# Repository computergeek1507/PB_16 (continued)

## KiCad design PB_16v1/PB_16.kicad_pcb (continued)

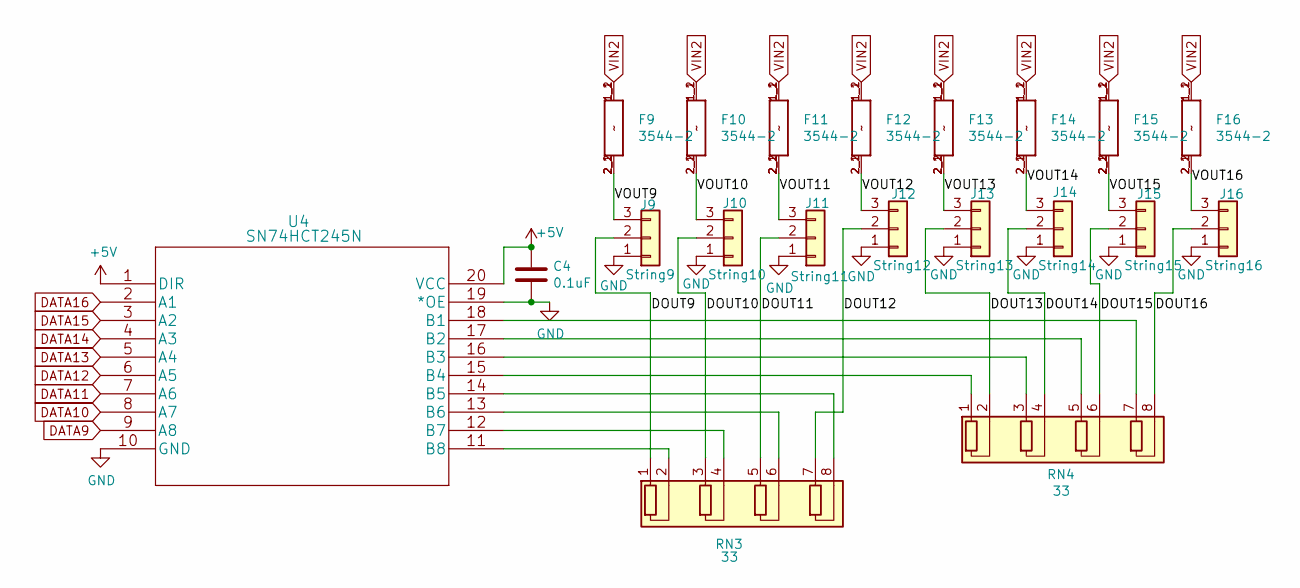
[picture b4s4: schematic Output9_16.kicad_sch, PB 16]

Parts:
C4: 0.1uF; C_Rect_L7.0mm_W2.0mm_P5.00mm; MPN SR215C104KARTR1; Digi-Key_PN 478-7336-1-ND
F9, F10, F11, F12, F13, F14, F15, F16: 3544-2; FUSE_3544-2; MPN 3544-2; Digi-Key_PN 36-3544-2-ND
J9: String9; PhoenixContact_MCV_1,5_3-G-3.5_1x03_P3.50mm_Vertical; MPN 1843619/OSTTJ0311530; Digi-Key_PN 277-5737-ND/ED10555-ND
J10: String10; PhoenixContact_MCV_1,5_3-G-3.5_1x03_P3.50mm_Vertical; MPN 1843619/OSTTJ0311530; Digi-Key_PN 277-5737-ND/ED10555-ND
J11: String11; PhoenixContact_MCV_1,5_3-G-3.5_1x03_P3.50mm_Vertical; MPN 1843619/OSTTJ0311530; Digi-Key_PN 277-5737-ND/ED10555-ND
J12: String12; PhoenixContact_MCV_1,5_3-G-3.5_1x03_P3.50mm_Vertical; MPN 1843619/OSTTJ0311530; Digi-Key_PN 277-5737-ND/ED10555-ND
J13: String13; PhoenixContact_MCV_1,5_3-G-3.5_1x03_P3.50mm_Vertical; MPN 1843619/OSTTJ0311530; Digi-Key_PN 277-5737-ND/ED10555-ND
J14: String14; PhoenixContact_MCV_1,5_3-G-3.5_1x03_P3.50mm_Vertical; MPN 1843619/OSTTJ0311530; Digi-Key_PN 277-5737-ND/ED10555-ND
J15: String15; PhoenixContact_MCV_1,5_3-G-3.5_1x03_P3.50mm_Vertical; MPN 1843619/OSTTJ0311530; Digi-Key_PN 277-5737-ND/ED10555-ND
J16: String16; PhoenixContact_MCV_1,5_3-G-3.5_1x03_P3.50mm_Vertical; MPN 1843619/OSTTJ0311530; Digi-Key_PN 277-5737-ND/ED10555-ND
RN3, RN4: 33; R_Array_SIP8; MPN 4608X-102-330LF; Digi-Key_PN 4608X-2-330LF-ND
U4: SN74HCT245N; MPN SN74HCT245N; Digi-Key_PN 296-1612-5-ND

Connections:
+5V: C4.1, U4.1 (DIR), U4.20 (VCC); also elsewhere on the board
/Output 9-16/DOUT9: J9.2, RN3.1 (R1.1)
/Output 9-16/DOUT10: J10.2, RN3.3 (R2.1)
/Output 9-16/DOUT11: J11.2, RN3.5 (R3.1)
/Output 9-16/DOUT12: J12.2, RN3.7 (R4.1)
/Output 9-16/DOUT13: J13.2, RN4.2 (R1.2)
/Output 9-16/DOUT14: J14.2, RN4.4 (R2.2)
/Output 9-16/DOUT15: J15.2, RN4.6 (R3.2)
/Output 9-16/DOUT16: J16.2, RN4.8 (R4.2)
/Output 9-16/VOUT9: F9.2_1 (2), F9.2_2 (2), J9.3
/Output 9-16/VOUT10: F10.2_1 (2), F10.2_2 (2), J10.3
/Output 9-16/VOUT11: F11.2_1 (2), F11.2_2 (2), J11.3
/Output 9-16/VOUT12: F12.2_1 (2), F12.2_2 (2), J12.3
/Output 9-16/VOUT13: F13.2_1 (2), F13.2_2 (2), J13.3
/Output 9-16/VOUT14: F14.2_1 (2), F14.2_2 (2), J14.3
/Output 9-16/VOUT15: F15.2_1 (2), F15.2_2 (2), J15.3
/Output 9-16/VOUT16: F16.2_1 (2), F16.2_2 (2), J16.3
DATA9: U4.9 (A8); also elsewhere on the board
DATA10: U4.8 (A7); also elsewhere on the board
DATA11: U4.7 (A6); also elsewhere on the board
DATA12: U4.6 (A5); also elsewhere on the board
DATA13: U4.5 (A4); also elsewhere on the board
DATA14: U4.4 (A3); also elsewhere on the board
DATA15: U4.3 (A2); also elsewhere on the board
DATA16: U4.2 (A1); also elsewhere on the board
GND: C4.2, J9.1, J10.1, J11.1, J12.1, J13.1, J14.1, J15.1, J16.1, U4.10 (GND), U4.19 (*OE); also elsewhere on the board
unnamed: RN3.2 (R1.2), U4.11 (B8)
unnamed: RN3.4 (R2.2), U4.12 (B7)
unnamed: RN3.6 (R3.2), U4.13 (B6)
unnamed: RN3.8 (R4.2), U4.14 (B5)
unnamed: RN4.1 (R1.1), U4.15 (B4)
unnamed: RN4.3 (R2.1), U4.16 (B3)
unnamed: RN4.5 (R3.1), U4.17 (B2)
unnamed: RN4.7 (R4.1), U4.18 (B1)
VIN2: F9.1_1 (1), F9.1_2 (1), F10.1_1 (1), F10.1_2 (1), F11.1_1 (1), F11.1_2 (1), F12.1_1 (1), F12.1_2 (1), F13.1_1 (1), F13.1_2 (1), F14.1_1 (1), F14.1_2 (1), F15.1_1 (1), F15.1_2 (1), F16.1_1 (1), F16.1_2 (1); also elsewhere on the board

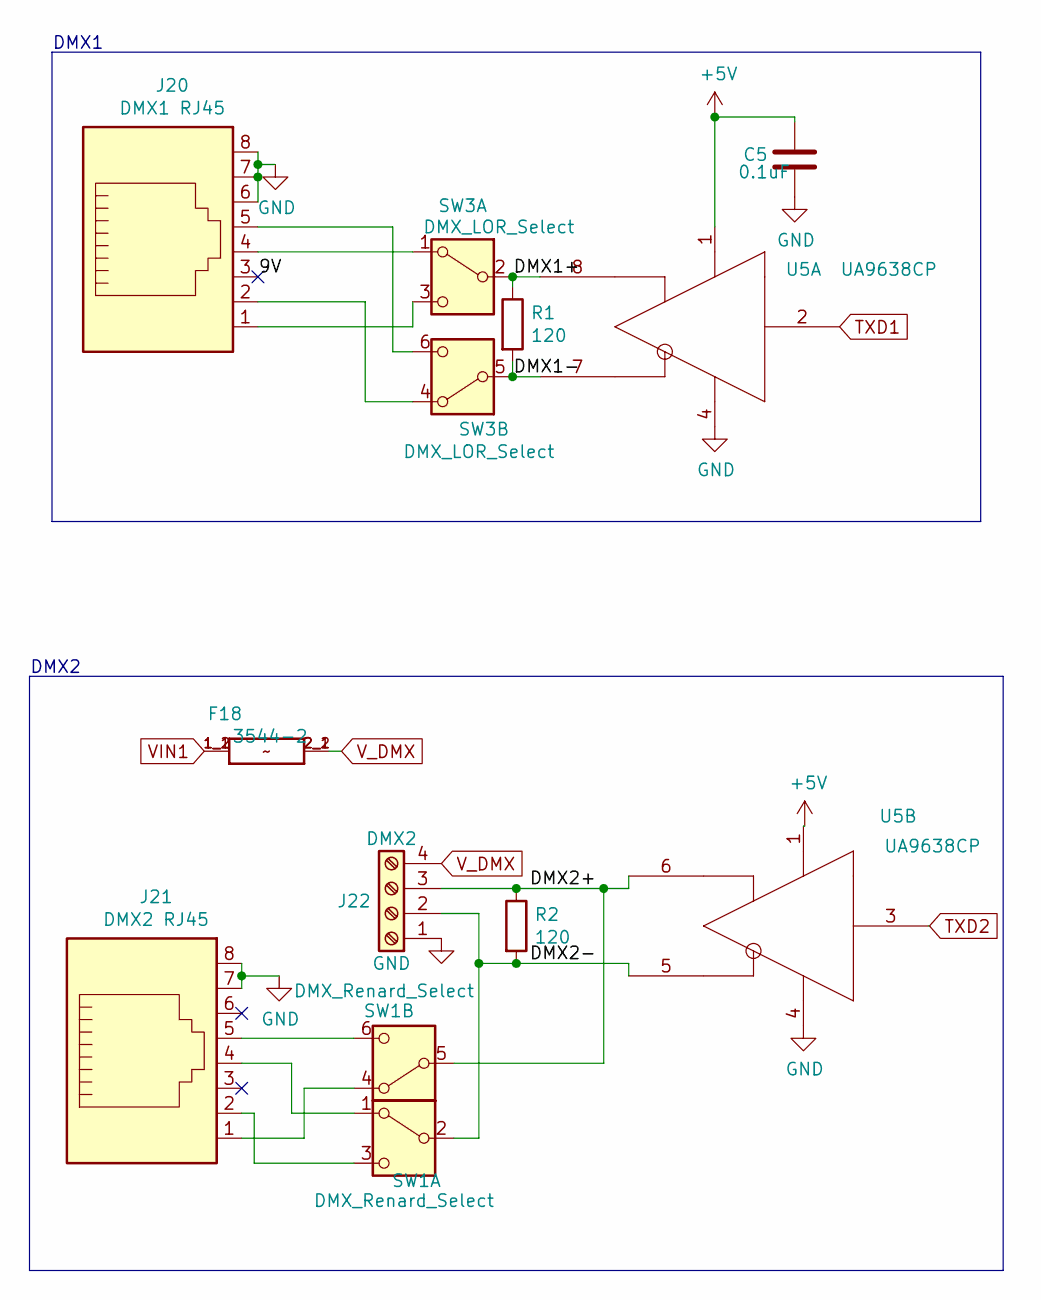
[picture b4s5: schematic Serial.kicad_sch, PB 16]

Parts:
C5: 0.1uF; C_Rect_L7.0mm_W2.0mm_P5.00mm; MPN SR215C104KARTR1; Digi-Key_PN 478-7336-1-ND
F18: 3544-2; FUSE_3544-2; MPN 3544-2; Digi-Key_PN 36-3544-2-ND
J20: DMX1 RJ45; RJ45_Amphenol_54602-x08_Horizontal; MPN A-2014-2-4-R; Digi-Key_PN AE10392-ND
J21: DMX2 RJ45; RJ45_Amphenol_54602-x08_Horizontal; MPN A-2014-2-4-R; Digi-Key_PN AE10392-ND
J22: DMX2; TerminalBlock_Phoenix_MKDS-1,5-4_1x04_P5.00mm_Horizontal; MPN 1729034; Digi-Key_PN 277-1238-ND
R1, R2: 120; R_Axial_DIN0207_L6.3mm_D2.5mm_P7.62mm_Horizontal; MPN CF14JT120R; Digi-Key_PN CF14JT120RCT-ND
SW1: DMX_Renard_Select; SW_CK_JS202011CQN_DPDT_Straight; MPN JS202011CQN; Digi-Key_PN 401-2001-ND
SW3: DMX_LOR_Select; SW_CK_JS202011CQN_DPDT_Straight; MPN JS202011CQN; Digi-Key_PN 401-2001-ND
U5: UA9638CP; DIP-8_W7.62mm; MPN UA9638CP; Digi-Key_PN 296-15059-5-ND

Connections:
+5V: C5.1, U5.1 (VCC); also elsewhere on the board
/Serial/9V: J20.3
/Serial/DMX1+: R1.1, SW3.2 (B), U5.8 (OUTB)
/Serial/DMX1-: R1.2, SW3.5 (B), U5.7 (OUTA)
/Serial/DMX2+: J22.3, R2.1, SW1.5 (B), U5.6 (OUTB)
/Serial/DMX2-: J22.2, R2.2, SW1.2 (B), U5.5 (OUTA)
GND: C5.2, J20.6, J20.7, J20.8, J21.7, J21.8, J22.1, U5.4 (GND); also elsewhere on the board
unnamed: J21.4, SW1.1 (A)
unnamed: J21.2, SW1.3 (C)
unnamed: J21.1, SW1.4 (A)
unnamed: J21.5, SW1.6 (C)
unnamed: J20.4, SW3.1 (A)
unnamed: J20.1, SW3.3 (C)
unnamed: J20.2, SW3.4 (A)
unnamed: J20.5, SW3.6 (C)
TXD1: U5.2 (IN); also elsewhere on the board
TXD2: U5.3 (IN); also elsewhere on the board
VIN1: F18.1_1 (1), F18.1_2 (1); also elsewhere on the board
V_DMX: F18.2_1 (2), F18.2_2 (2), J22.4

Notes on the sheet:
DMX2
DMX1

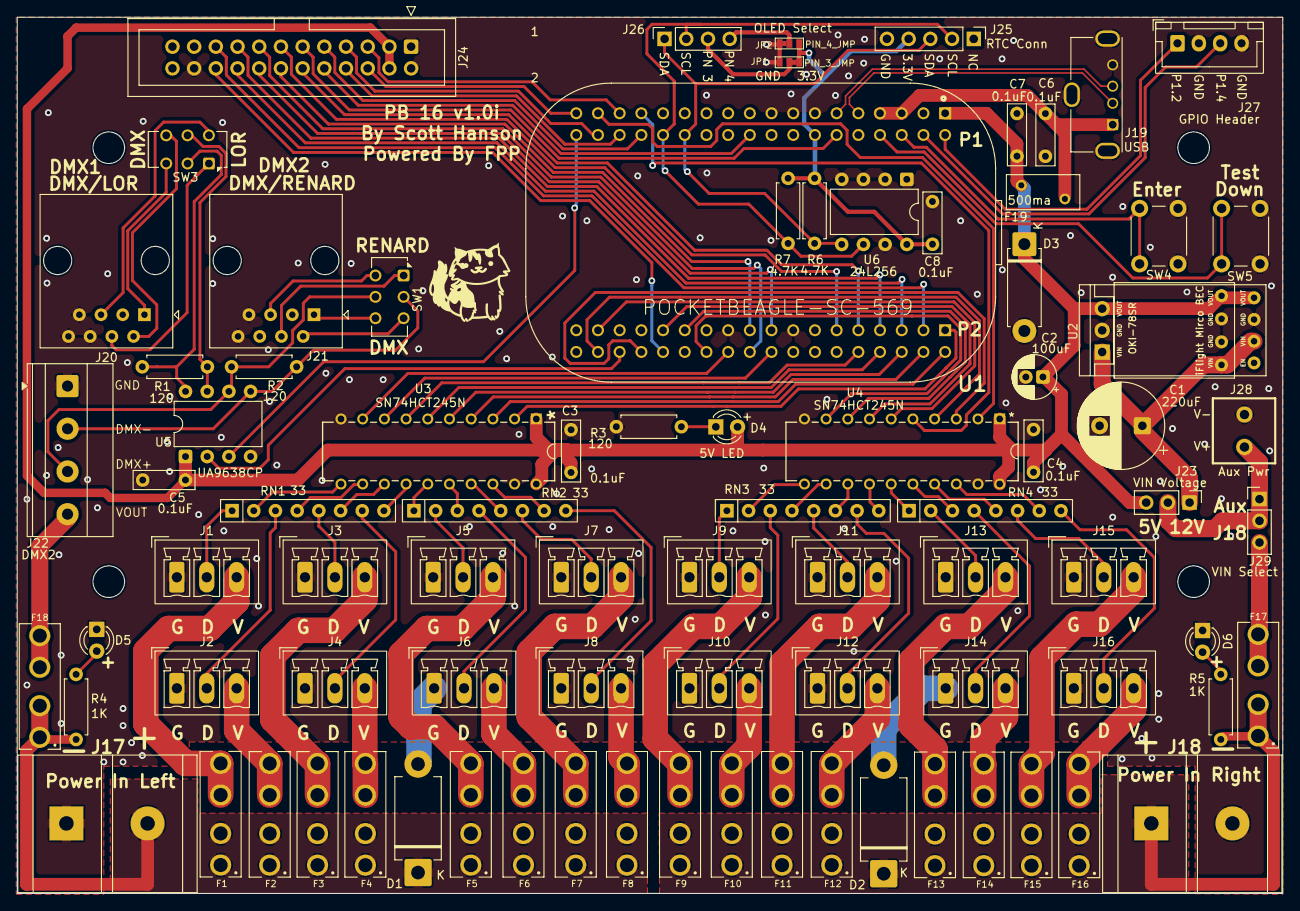
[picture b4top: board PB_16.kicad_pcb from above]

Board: 2 copper layers, 148.1 x 102.6 mm, 89 parts (0 on the bottom side), 117 nets.

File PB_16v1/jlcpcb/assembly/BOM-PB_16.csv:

Comment,Designator,Footprint,LCSC
100uF,C2,CP_Radial_D5.0mm_P2.00mm,
0.1uF,C4,C_Rect_L7.0mm_W2.0mm_P5.00mm,
String2,J2,"PhoenixContact_MCV_1,5_3-G-3.5_1x03_P3.50mm_Vertical",
String5,J5,"PhoenixContact_MCV_1,5_3-G-3.5_1x03_P3.50mm_Vertical",
String6,J6,"PhoenixContact_MCV_1,5_3-G-3.5_1x03_P3.50mm_Vertical",
String7,J7,"PhoenixContact_MCV_1,5_3-G-3.5_1x03_P3.50mm_Vertical",
String8,J8,"PhoenixContact_MCV_1,5_3-G-3.5_1x03_P3.50mm_Vertical",
String9,J9,"PhoenixContact_MCV_1,5_3-G-3.5_1x03_P3.50mm_Vertical",
String10,J10,"PhoenixContact_MCV_1,5_3-G-3.5_1x03_P3.50mm_Vertical",
String11,J11,"PhoenixContact_MCV_1,5_3-G-3.5_1x03_P3.50mm_Vertical",
String12,J12,"PhoenixContact_MCV_1,5_3-G-3.5_1x03_P3.50mm_Vertical",
String13,J13,"PhoenixContact_MCV_1,5_3-G-3.5_1x03_P3.50mm_Vertical",
String14,J14,"PhoenixContact_MCV_1,5_3-G-3.5_1x03_P3.50mm_Vertical",
String15,J15,"PhoenixContact_MCV_1,5_3-G-3.5_1x03_P3.50mm_Vertical",
String16,J16,"PhoenixContact_MCV_1,5_3-G-3.5_1x03_P3.50mm_Vertical",
SN74HCT245N,U4,SN74HCT245N,
3544-2,F1,FUSE_3544-2,
3544-2,F7,FUSE_3544-2,
3544-2,F14,FUSE_3544-2,
SB5100-T,D2,D_DO-201AD_P12.70mm_Horizontal,
0.1uF,C3,C_Rect_L7.0mm_W2.0mm_P5.00mm,
3544-2,F2,FUSE_3544-2,
3544-2,F6,FUSE_3544-2,
3544-2,F8,FUSE_3544-2,
3544-2,F9,FUSE_3544-2,
3544-2,F10,FUSE_3544-2,
3544-2,F16,FUSE_3544-2,
3544-2,F5,FUSE_3544-2,
3544-2,F3,FUSE_3544-2,
3544-2,F13,FUSE_3544-2,
33,RN1,R_Array_SIP8,
3544-2,F11,FUSE_3544-2,
33,RN3,R_Array_SIP8,
33,RN4,R_Array_SIP8,
33,RN2,R_Array_SIP8,
3544-2,F4,FUSE_3544-2,
String1,J1,"PhoenixContact_MCV_1,5_3-G-3.5_1x03_P3.50mm_Vertical",
String3,J3,"PhoenixContact_MCV_1,5_3-G-3.5_1x03_P3.50mm_Vertical",
String4,J4,"PhoenixContact_MCV_1,5_3-G-3.5_1x03_P3.50mm_Vertical",
SB5100-T,D1,D_DO-201AD_P12.70mm_Horizontal,
USB,J19,USB_A_Molex_105057_Vertical,
120,R1,R_Axial_DIN0207_L6.3mm_D2.5mm_P7.62mm_Horizontal,
120,R2,R_Axial_DIN0207_L6.3mm_D2.5mm_P7.62mm_Horizontal,
RTC Conn,J25,PinHeader_1x05_P2.54mm_Vertical,
3544-2,F15,FUSE_3544-2,
3544-2,F12,FUSE_3544-2,
Expansion Header,J24,IDC-Header_2x20_P2.54mm_Vertical,
Universe5V,U2,Universal_5V_Horizontal,
SN74HCT245N,U3,SN74HCT245N,
500ma,F19,Fuse_BelFuse_0ZRE0005FF_L8.3mm_W3.8mm,
DMX_Renard_Select,SW1,SW_CuK_JS202011CQN_DPDT_Straight,
0.1uF,C6,C_Rect_L7.0mm_W2.0mm_P5.00mm,
0.1uF,C7,C_Rect_L7.0mm_W2.0mm_P5.00mm,
POCKETBEAGLE-SC-569,U1,BEAGLE_POCKETBEAGLE-SC-569,
OLED Select,J26,PinSocket_1x04_P2.54mm_Vertical,
DMX2 RJ45,J21,RJ45_Amphenol_54602-x08_Horizontal,
VIN1 LED,D5,LED_D3.0mm_Clear,
VIN2 LED,D6,LED_D3.0mm_Clear,
1K,R4,R_Axial_DIN0207_L6.3mm_D2.5mm_P7.62mm_Horizontal,
1K,R5,R_Axial_DIN0207_L6.3mm_D2.5mm_P7.62mm_Horizontal,
VIN Voltage,J23,PinHeader_1x03_P2.54mm_Vertical,
5V LED,D4,LED_D3.0mm_Clear,
120,R3,R_Axial_DIN0207_L6.3mm_D2.5mm_P7.62mm_Horizontal,
GPIO Header,J27,JST_XH_B4B-XH-A_1x04_P2.50mm_Vertical,
OLED Select,SW2,SW_CuK_JS202011CQN_DPDT_Straight,
3544-2,F17,FUSE_3544-2,
VIN Select,J29,PinHeader_1x03_P2.54mm_Vertical,
Aux Pwr,J28,PHOENIX_MKDS1%2f2-3.81,
220uF,C1,CP_Radial_D10.0mm_P5.00mm,
4.7K,R6,R_Axial_DIN0207_L6.3mm_D2.5mm_P7.62mm_Horizontal,
4.7K,R7,R_Axial_DIN0207_L6.3mm_D2.5mm_P7.62mm_Horizontal,
24L256,U6,DIP-8_W7.62mm,
0.1uF,C8,C_Rect_L7.0mm_W2.0mm_P5.00mm,
Enter BTN,SW4,SW_PUSH_6mm,
Down BTN,SW5,SW_PUSH_6mm,
0.1uF,C5,C_Rect_L7.0mm_W2.0mm_P5.00mm,
DMX2,J22,"TerminalBlock_Phoenix_MKDS-1,5-4_1x04_P5.00mm_Horizontal",
UA9638CP,U5,DIP-8_W7.62mm,
DMX1 RJ45,J20,RJ45_Amphenol_54602-x08_Horizontal,
Zener 5.1V,D3,D_5W_P10.16mm_Horizontal,
Power In Right,J18,BARRIER_BLOCK_1ROW_2POS_P9.5MM,
Power In Left,J17,BARRIER_BLOCK_1ROW_2POS_P9.5MM,
DMX_LOR_Select,SW3,SW_CuK_JS202011CQN_DPDT_Straight,
3544-2,F18,FUSE_3544-2,

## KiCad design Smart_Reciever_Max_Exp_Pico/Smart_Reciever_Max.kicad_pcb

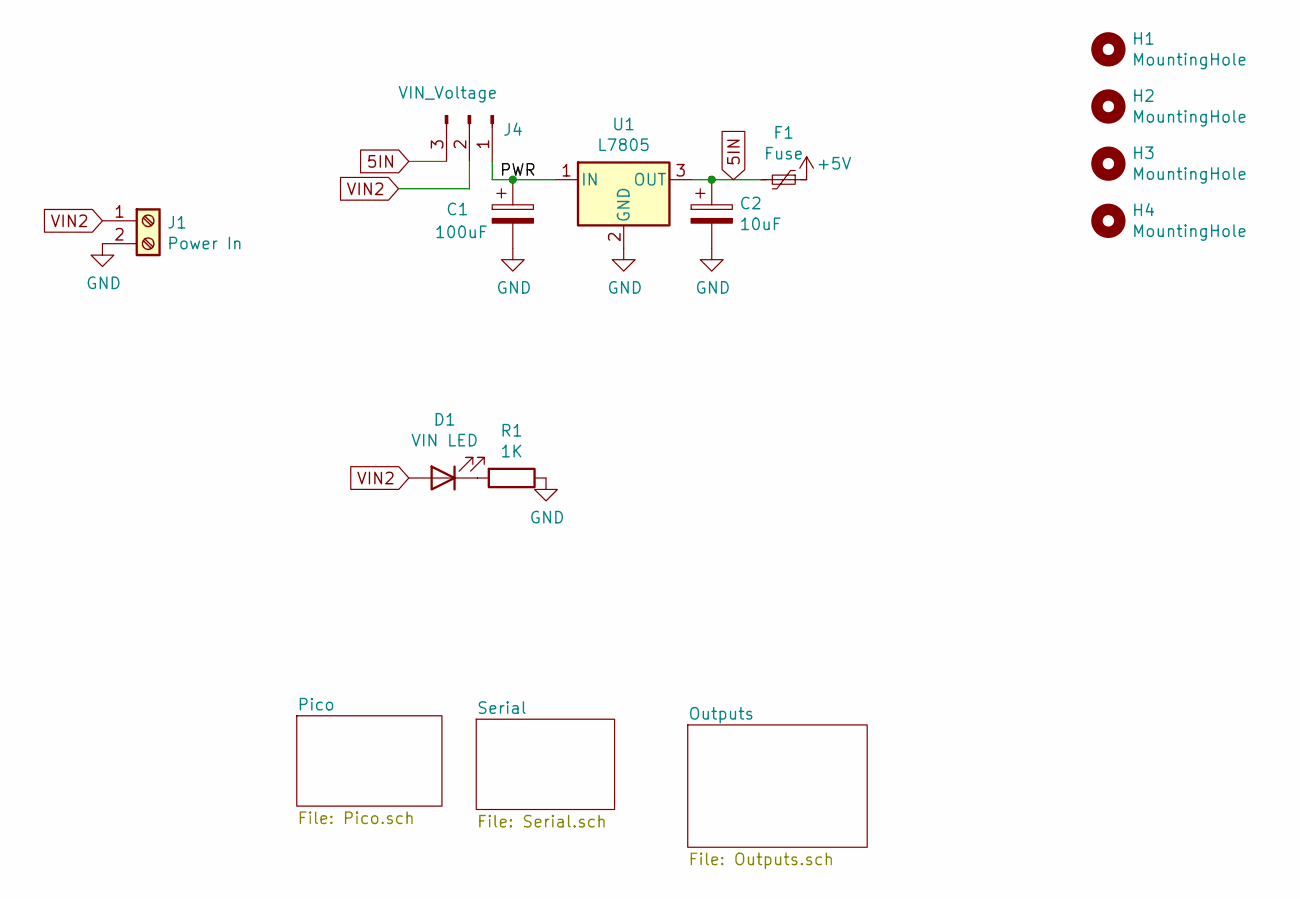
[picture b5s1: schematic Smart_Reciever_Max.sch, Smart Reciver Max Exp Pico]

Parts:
C1: 100uF; CP_Radial_D5.0mm_P2.00mm; MPN 16ZLH100MEFC5X11; Digi-Key_PN 1189-1148-ND
C2: 10uF; CP_Radial_D5.0mm_P2.00mm; MPN UVR1H100MDD; Digi-Key_PN 493-1103-ND
D1: VIN LED; LED_D3.0mm_Clear; MPN WP3A8GD; Digi-Key_PN 754-1217-ND
F1: Fuse; Fuse_BelFuse_0ZRE0005FF_L8.3mm_W3.8mm; MPN RXEF050-2; Digi-Key_PN RXEF050-2HFCT-ND
H1, H2, H3, H4: MountingHole; MountingHole_4.3mm_M4
J1: Power In; TerminalBlock_Phoenix_MKDS-1,5-2_1x02_P5.00mm_Horizontal; MPN 1729018; Digi-Key_PN 277-1236-ND
J4: VIN_Voltage; PinHeader_1x03_P2.54mm_Vertical; MPN 61300311121; Digi-Key_PN 732-5316-ND
R1: 1K; R_Axial_DIN0207_L6.3mm_D2.5mm_P7.62mm_Horizontal; MPN CF14JT1K00; Digi-Key_PN CF14JT1K00CT-ND
U1: L7805; TO-220-3_Vertical; MPN MC7805CTG; Digi-Key_PN MC7805CTGOS-ND

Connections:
5IN: C2.1, F1.2, J4.3, U1.3 (OUT)
+5V: F1.1; also elsewhere on the board
/PWR: C1.1, J4.1, U1.1 (IN)
GND: C1.2, C2.2, J1.2, R1.1, U1.2 (GND); also elsewhere on the board
unnamed: D1.1 (K), R1.2
VIN2: D1.2 (A), J1.1, J4.2

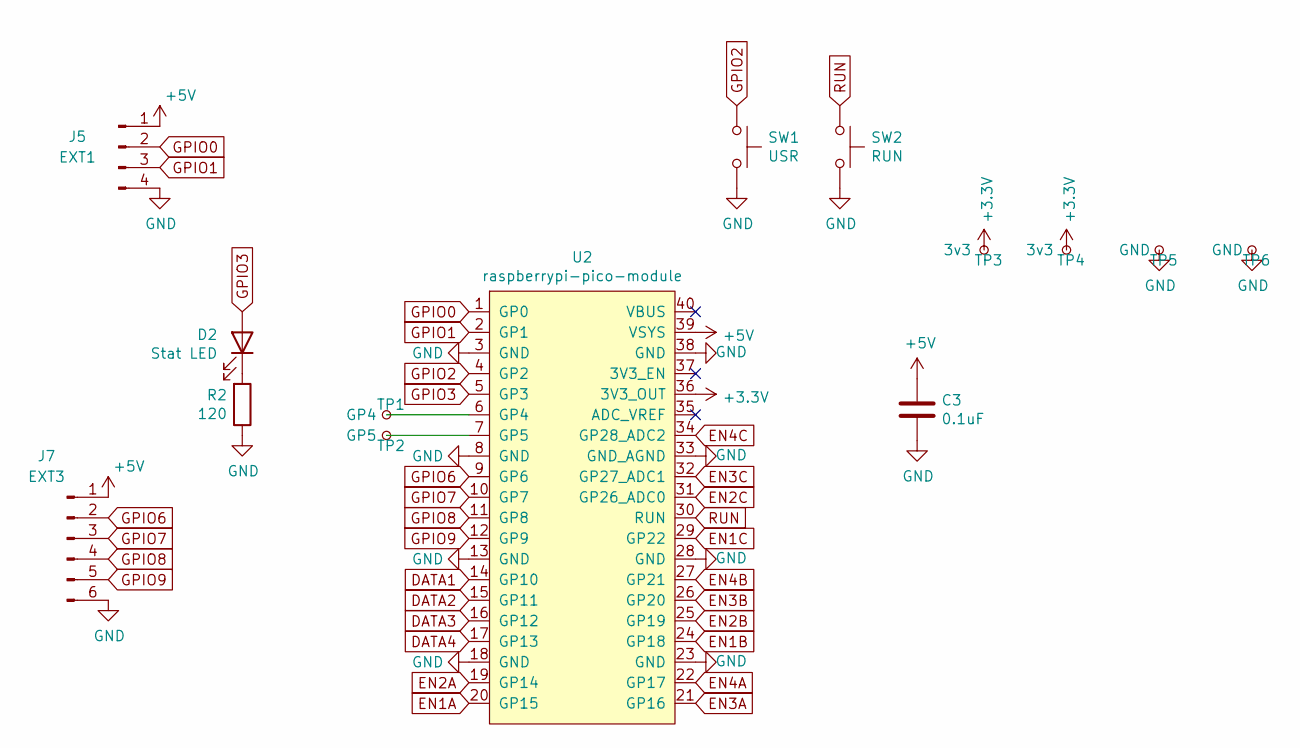
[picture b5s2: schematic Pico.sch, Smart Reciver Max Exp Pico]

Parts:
C3: 0.1uF; C_Rect_L7.0mm_W2.0mm_P5.00mm; MPN SR215C104KARTR1; Digi-Key_PN 478-7336-1-ND
D2: Stat LED; LED_D3.0mm_Clear; MPN WP3A8GD; Digi-Key_PN 754-1217-ND
J5: EXT1; PinHeader_1x04_P2.54mm_Vertical
J7: EXT3; PinHeader_1x06_P2.54mm_Vertical
R2: 120; R_Axial_DIN0207_L6.3mm_D2.5mm_P7.62mm_Horizontal; MPN CF14JT120R; Digi-Key_PN CF14JT120RCT-ND
SW1: USR; SW_PUSH_6mm; MPN 1825910-6; Digi-Key_PN 450-1650-ND
SW2: RUN; SW_PUSH_6mm; MPN 1825910-6; Digi-Key_PN 450-1650-ND
TP1: GP4; TestPoint_THTPad_1.0x1.0mm_Drill0.5mm
TP2: GP5; TestPoint_THTPad_1.0x1.0mm_Drill0.5mm
TP3, TP4: 3v3; TestPoint_THTPad_1.0x1.0mm_Drill0.5mm
TP5, TP6: GND; TestPoint_THTPad_1.0x1.0mm_Drill0.5mm
U2: raspberrypi-pico-module; raspberrypi-pico-module-nohole; MPN SC0915; Digi-Key_PN 2648-SC0915CT-ND

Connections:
+3V3: TP3.1, TP4.1, U2.36 (3V3_OUT); also elsewhere on the board
+5V: C3.1, J5.1, J7.1, U2.39 (VSYS); also elsewhere on the board
DATA1: U2.14 (GP10); also elsewhere on the board
DATA2: U2.15 (GP11); also elsewhere on the board
DATA3: U2.16 (GP12); also elsewhere on the board
DATA4: U2.17 (GP13); also elsewhere on the board
EN1A: U2.20 (GP15); also elsewhere on the board
EN1B: U2.24 (GP18); also elsewhere on the board
EN1C: U2.29 (GP22); also elsewhere on the board
EN2A: U2.19 (GP14); also elsewhere on the board
EN2B: U2.25 (GP19); also elsewhere on the board
EN2C: U2.31 (GP26_ADC0); also elsewhere on the board
EN3A: U2.21 (GP16); also elsewhere on the board
EN3B: U2.26 (GP20); also elsewhere on the board
EN3C: U2.32 (GP27_ADC1); also elsewhere on the board
EN4A: U2.22 (GP17); also elsewhere on the board
EN4B: U2.27 (GP21); also elsewhere on the board
EN4C: U2.34 (GP28_ADC2); also elsewhere on the board
GND: C3.2, J5.4, J7.6, R2.1, SW1.2, SW2.2, TP5.1, TP6.1, U2.3 (GND), U2.8 (GND), U2.13 (GND), U2.18 (GND), U2.23 (GND), U2.28 (GND), U2.33 (GND_AGND), U2.38 (GND); also elsewhere on the board
GPIO0: J5.2, U2.1 (GP0)
GPIO1: J5.3, U2.2 (GP1)
GPIO2: SW1.1, U2.4 (GP2)
GPIO3: D2.2 (A), U2.5 (GP3)
GPIO6: J7.2, U2.9 (GP6)
GPIO7: J7.3, U2.10 (GP7)
GPIO8: J7.4, U2.11 (GP8)
GPIO9: J7.5, U2.12 (GP9)
unnamed: D2.1 (K), R2.2
unnamed: TP1.1, U2.6 (GP4)
unnamed: TP2.1, U2.7 (GP5)
RUN: SW2.1, U2.30 (RUN)

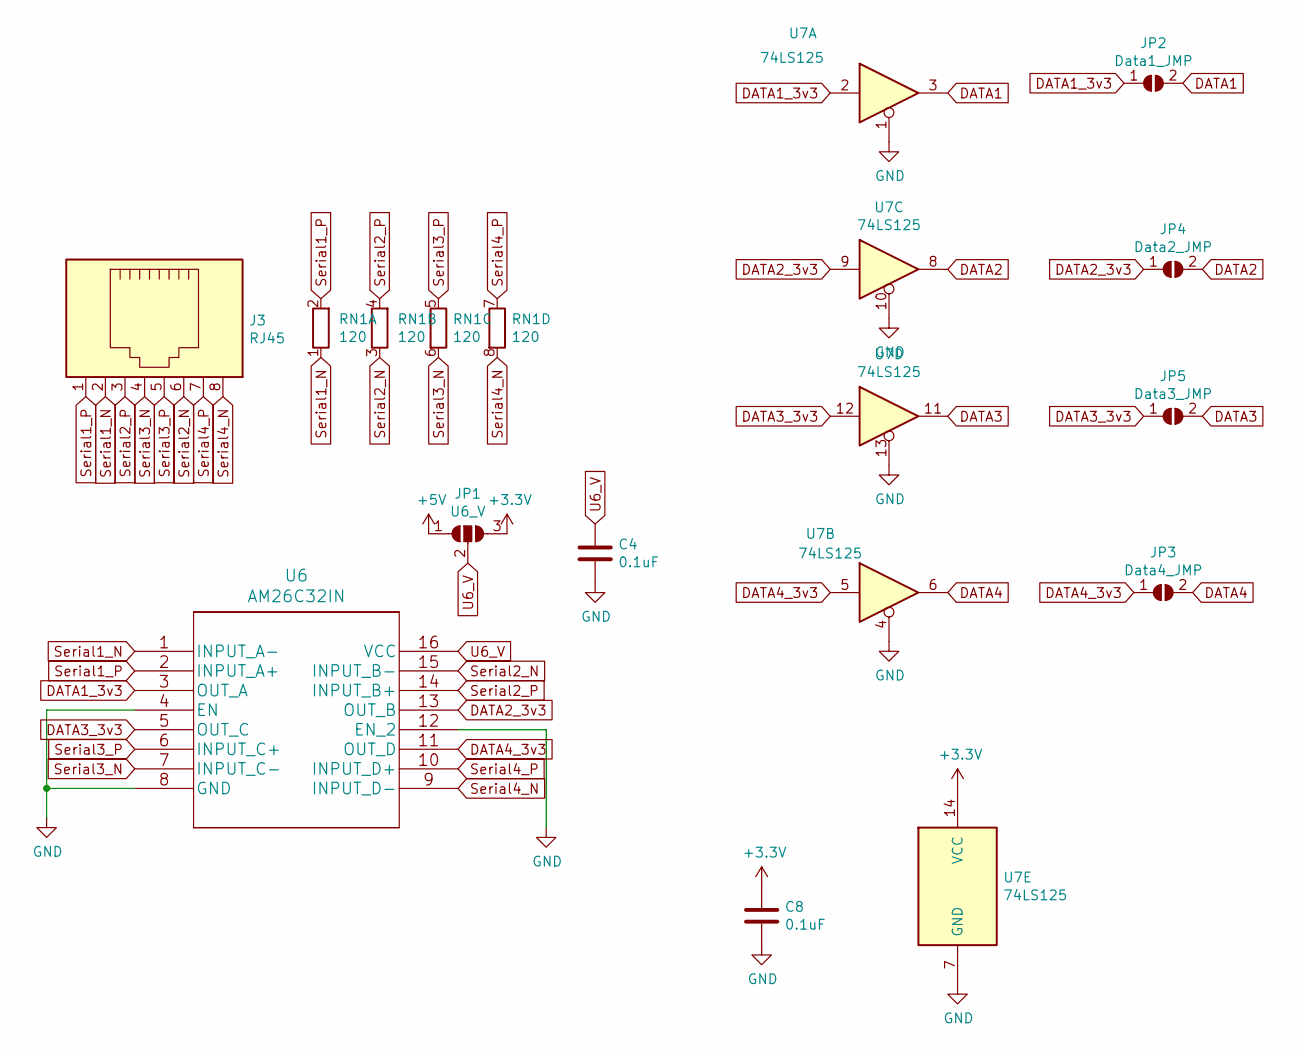
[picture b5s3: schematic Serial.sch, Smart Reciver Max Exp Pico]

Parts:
C4, C8: 0.1uF; C_Rect_L7.0mm_W2.0mm_P5.00mm; MPN SR215C104KARTR1; Digi-Key_PN 478-7336-1-ND
J3: RJ45; RJ45_Amphenol_54602-x08_Horizontal; MPN A-2014-2-4-R; Digi-Key_PN AE10392-ND
JP1: U6_V; SolderJumper-3_P2.0mm_Open_TrianglePad1.0x1.5mm
JP2: Data1_JMP; SolderJumper-2_P1.3mm_Open_TrianglePad1.0x1.5mm
JP3: Data4_JMP; SolderJumper-2_P1.3mm_Open_TrianglePad1.0x1.5mm
JP4: Data2_JMP; SolderJumper-2_P1.3mm_Open_TrianglePad1.0x1.5mm
JP5: Data3_JMP; SolderJumper-2_P1.3mm_Open_TrianglePad1.0x1.5mm
RN1: 120; R_Array_SIP8; MPN 4608X-102-121LF; Digi-Key_PN 4608X-2-121LF-ND
U6: AM26C32IN; DIP-16_W7.62mm_LongPads; MPN AM26C32IN; Digi-Key_PN 296-6789-5-ND
U7: 74LS125; DIP-14_W7.62mm_LongPads; MPN SN74AHC125N; Digi-Key_PN 296-4531-5-ND

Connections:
+3V3: C8.1, JP1.3 (B), U7.14 (VCC); also elsewhere on the board
+5V: JP1.1 (A); also elsewhere on the board
DATA1: JP2.2 (B), U7.3; also elsewhere on the board
DATA1_3v3: JP2.1 (A), U6.3 (OUT_A), U7.2
DATA2: JP4.2 (B), U7.8; also elsewhere on the board
DATA2_3v3: JP4.1 (A), U6.13 (OUT_B), U7.9
DATA3: JP5.2 (B), U7.11; also elsewhere on the board
DATA3_3v3: JP5.1 (A), U6.5 (OUT_C), U7.12
DATA4: JP3.2 (B), U7.6; also elsewhere on the board
DATA4_3v3: JP3.1 (A), U6.11 (OUT_D), U7.5
GND: C4.2, C8.2, U6.4 (EN), U6.8 (GND), U6.12 (EN_2), U7.1, U7.4, U7.7 (GND), U7.10, U7.13; also elsewhere on the board
Serial1_N: J3.2, RN1.1 (R1.1), U6.1 (INPUT_A-)
Serial1_P: J3.1, RN1.2 (R1.2), U6.2 (INPUT_A+)
Serial2_N: J3.6, RN1.3 (R2.1), U6.15 (INPUT_B-)
Serial2_P: J3.3, RN1.4 (R2.2), U6.14 (INPUT_B+)
Serial3_N: J3.4, RN1.6 (R3.2), U6.7 (INPUT_C-)
Serial3_P: J3.5, RN1.5 (R3.1), U6.6 (INPUT_C+)
Serial4_N: J3.8, RN1.8 (R4.2), U6.9 (INPUT_D-)
Serial4_P: J3.7, RN1.7 (R4.1), U6.10 (INPUT_D+)
U6_V: C4.1, JP1.2 (C), U6.16 (VCC)

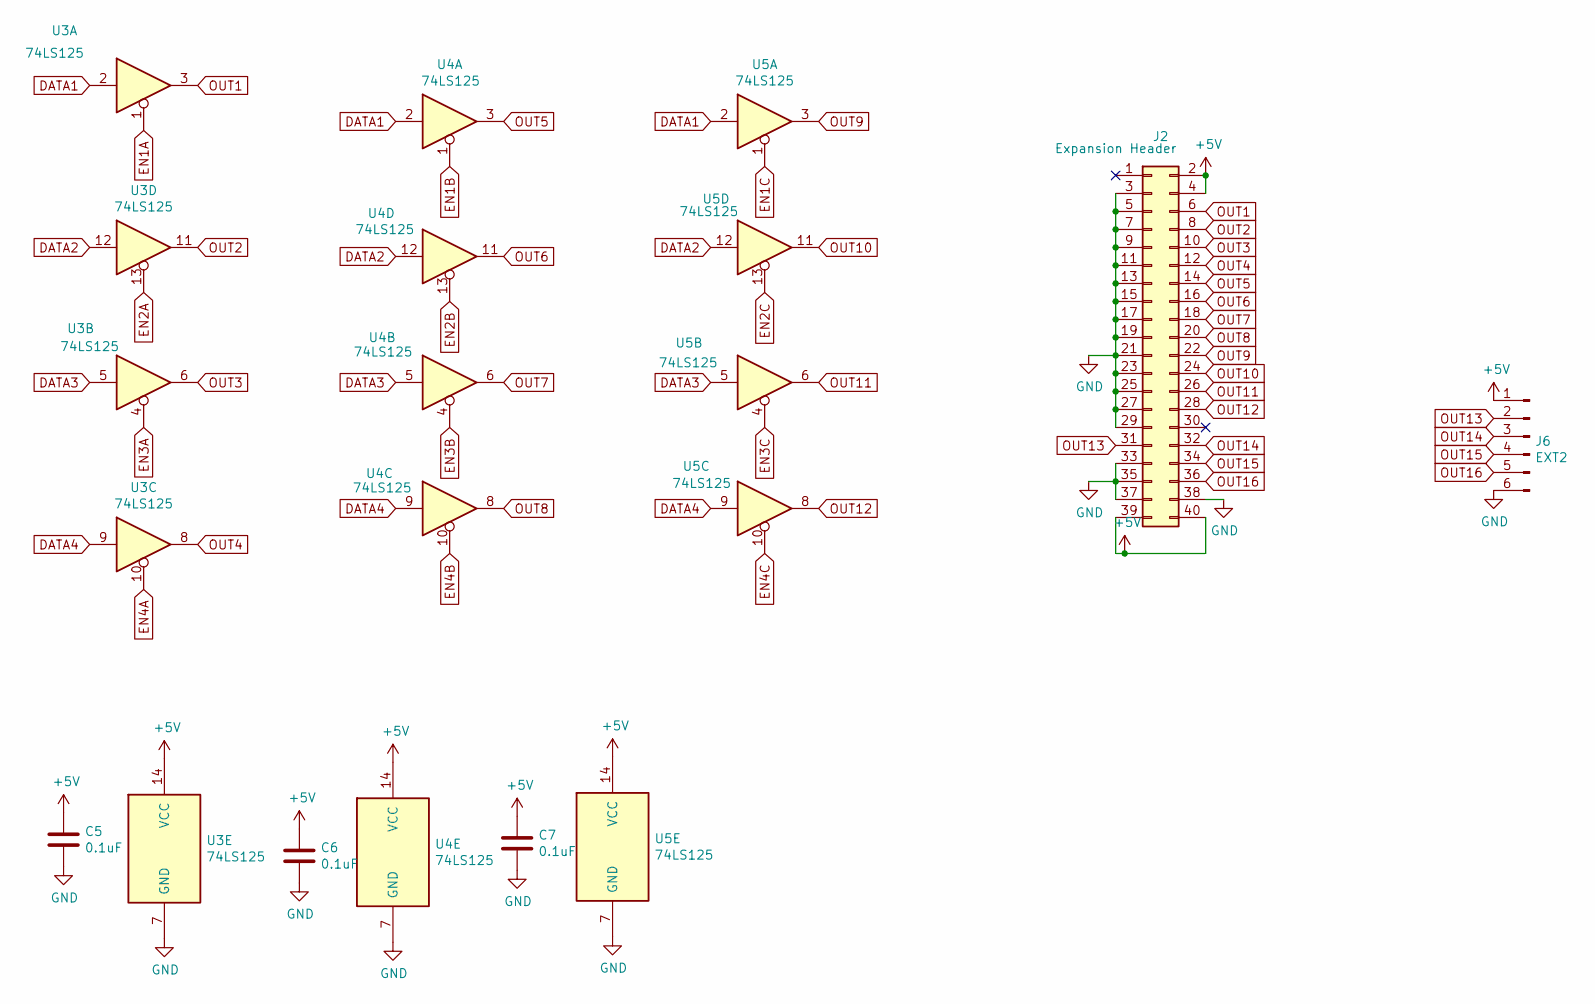
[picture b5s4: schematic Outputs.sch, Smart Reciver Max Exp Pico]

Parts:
C3, C5, C6: 0.1uF; C_Rect_L7.0mm_W2.0mm_P5.00mm; MPN SR215C104KARTR1; Digi-Key_PN 478-7336-1-ND
J2: Expansion Header; IDC-Header_2x20_P2.54mm_Vertical; MPN SBH11-PBPC-D20-ST-BK; Digi-Key_PN S9175-ND
J6: EXT2; PinHeader_1x06_P2.54mm_Vertical
U3, U4, U5: 74LS125; DIP-14_W7.62mm_LongPads; MPN SN74AHC125N; Digi-Key_PN 296-4531-5-ND

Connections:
+5V: C3.1, C5.1, C6.1, J2.2, J2.4, J2.39, J2.40, J6.1, U3.14 (VCC), U4.14 (VCC), U5.14 (VCC); also elsewhere on the board
DATA1: U3.2, U4.2, U5.2; also elsewhere on the board
DATA2: U3.12, U4.12, U5.12; also elsewhere on the board
DATA3: U3.5, U4.5, U5.5; also elsewhere on the board
DATA4: U3.9, U4.9, U5.9; also elsewhere on the board
EN1A: U3.1; also elsewhere on the board
EN1B: U4.1; also elsewhere on the board
EN1C: U5.1; also elsewhere on the board
EN2A: U3.13; also elsewhere on the board
EN2B: U4.13; also elsewhere on the board
EN2C: U5.13; also elsewhere on the board
EN3A: U3.4; also elsewhere on the board
EN3B: U4.4; also elsewhere on the board
EN3C: U5.4; also elsewhere on the board
EN4A: U3.10; also elsewhere on the board
EN4B: U4.10; also elsewhere on the board
EN4C: U5.10; also elsewhere on the board
GND: C3.2, C5.2, C6.2, J2.3, J2.5, J2.7, J2.9, J2.11, J2.13, J2.15, J2.17, J2.19, J2.21, J2.23, J2.25, J2.27, J2.29, J2.33, J2.35, J2.37, J2.38, J6.6, U3.7 (GND), U4.7 (GND), U5.7 (GND); also elsewhere on the board
OUT1: J2.6, U3.3
OUT2: J2.8, U3.11
OUT3: J2.10, U3.6
OUT4: J2.12, U3.8
OUT5: J2.14, U4.3
OUT6: J2.16, U4.11
OUT7: J2.18, U4.6
OUT8: J2.20, U4.8
OUT9: J2.22, U5.3
OUT10: J2.24, U5.11
OUT11: J2.26, U5.6
OUT12: J2.28, U5.8
OUT13: J2.31, J6.2
OUT14: J2.32, J6.3
OUT15: J2.34, J6.4
OUT16: J2.36, J6.5

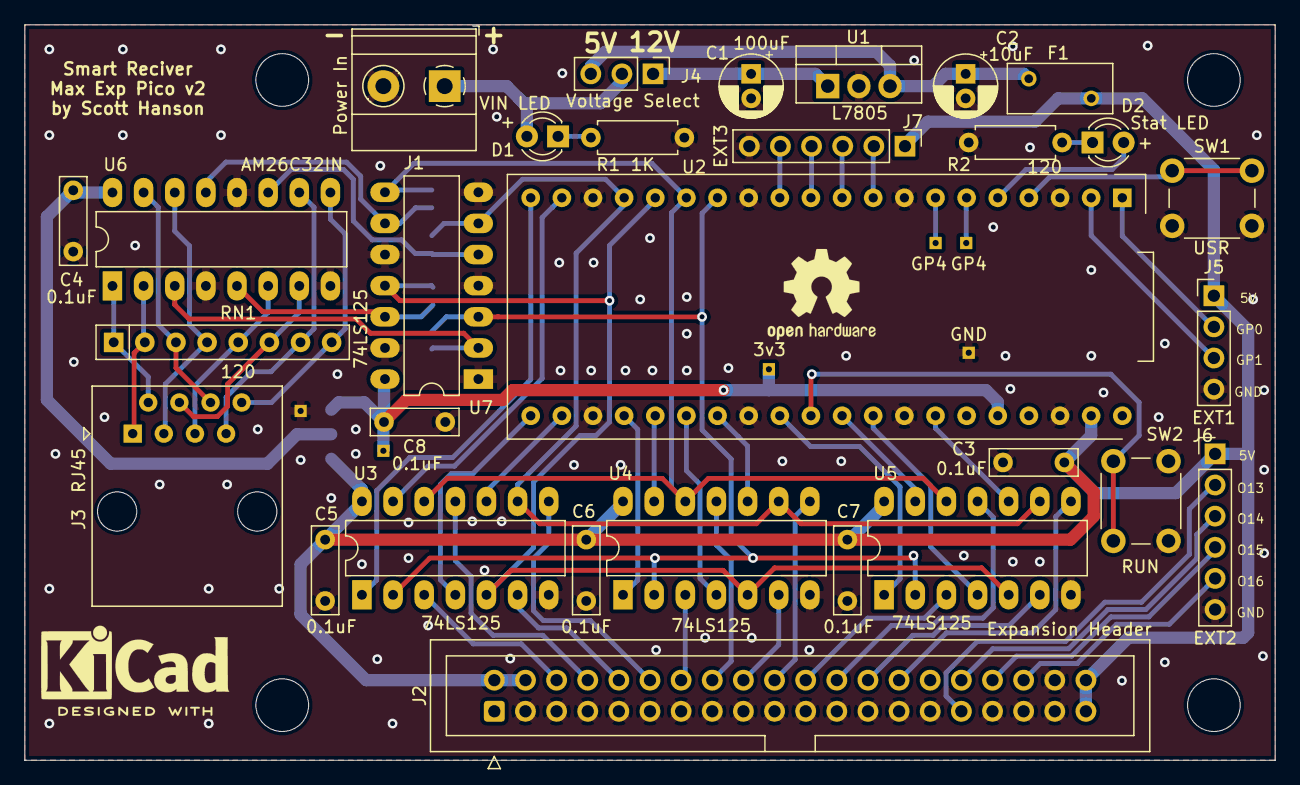
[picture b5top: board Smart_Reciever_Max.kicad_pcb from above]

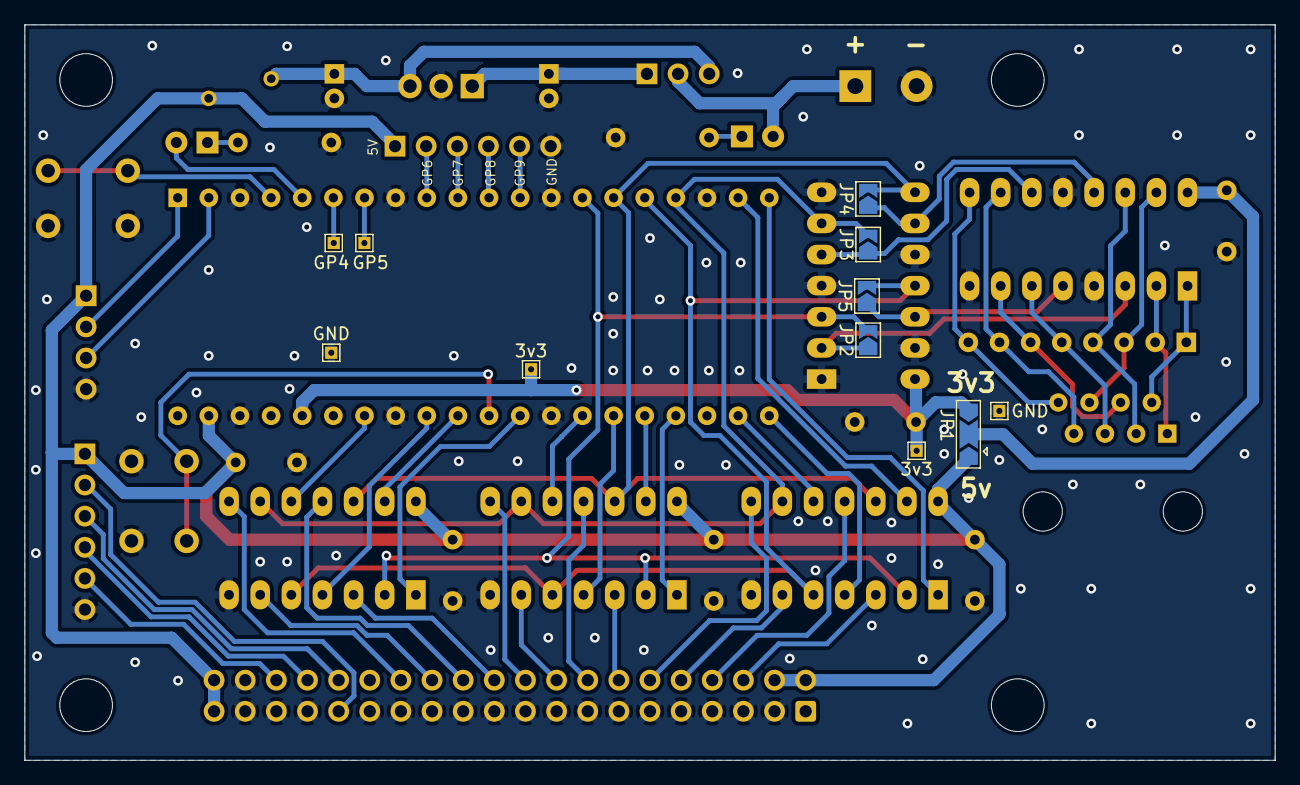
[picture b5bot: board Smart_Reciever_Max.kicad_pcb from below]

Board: 2 copper layers, 102.0 x 60.0 mm, 45 parts (11 on the bottom side), 64 nets.

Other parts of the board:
C7: 0.1uF; C_Rect_L7.0mm_W2.0mm_P5.00mm

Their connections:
+5V: C7.1; also elsewhere on the board
GND: C7.2; also elsewhere on the board
